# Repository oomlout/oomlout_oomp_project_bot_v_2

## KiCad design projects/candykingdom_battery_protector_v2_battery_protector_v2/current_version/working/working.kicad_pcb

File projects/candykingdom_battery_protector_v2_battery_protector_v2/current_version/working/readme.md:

# battery_protector_v2
 
## summary 
* id: candykingdom_battery_protector_v2_battery_protector_v2
* user: candykingdom
* name: battery_protector_v2
* board: battery_protector_v2
* repo: https://github.com/candykingdom/battery-protector-v2
* src_file_repo_kicad_pcb: battery-protector-v2.kicad_pcb
* src_file_repo_kicad_pcb_link: https://github.com/candykingdom/battery-protector-v2/tree/master/battery-protector-v2.kicad_pcb

* src_file_repo_sch: battery-protector-v2.sch
* src_file_repo_sch_link: https://github.com/candykingdom/battery-protector-v2/tree/master/battery-protector-v2.sch
* full details link: https://github.com/oomlout/oomlout_oomp_project_bot_v_2/tree/main/projects/candykingdom_battery_protector_v2_battery_protector_v2/current_version/working

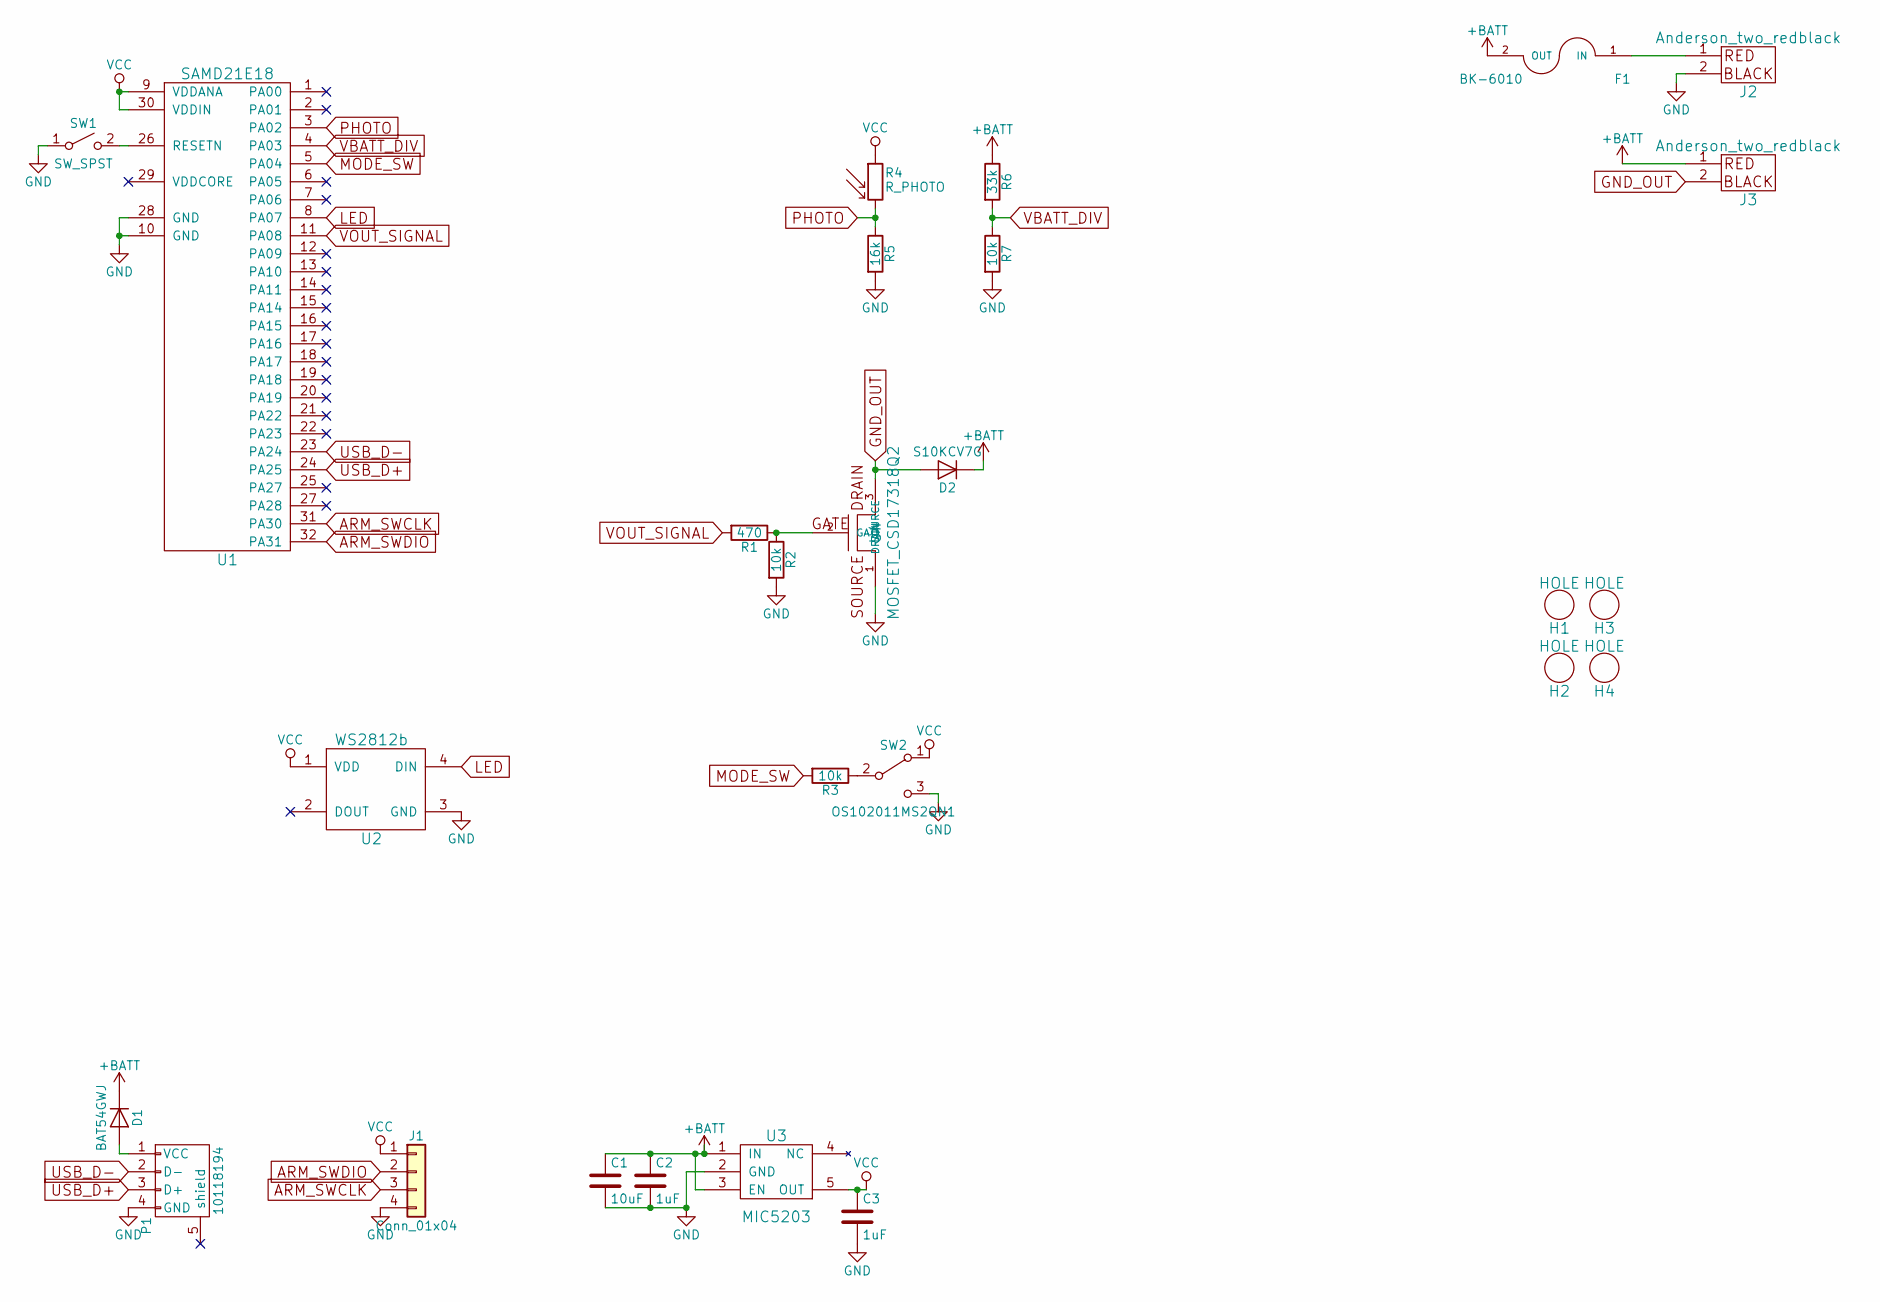
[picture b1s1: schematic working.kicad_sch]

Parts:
C1: 10uF; C_0805
C2, C3: 1uF; C_0603
D1: BAT54GWJ; D_SOD-123
D2: S10KCV7G; DIODE-DO-214AB
F1: BK-6010; FUSEHOLDER_ATC_Bk-6010
H1, H2, H3, H4: HOLE; HOLE_M4
J1: Conn_01x04; Pin_Header_Straight_1x04_Pitch2.54mm
J2, J3: Anderson_two_redblack; Anderson_1337G3_right_angle_bottom_two
P1: 10118194; FRAMATOME_10118194-0001LF
R1: 470; R_0603
R2, R3, R7: 10k; R_0603
R4: R_PHOTO
R5: 16k; R_0603
R6: 33k; R_0603
SW1: SW_SPST; TACTILE_SWITCH_SMD_4.6X2.8MM
SW2: OS102011MS2QN1; SW_2POS_OS102011MS2QN1
U1: SAMD21E18; TQFP32-08
U2: WS2812b; WS2812B
U3: MIC5203; SOT-23-5
U4: MOSFET_CSD17318Q2; TRANS_CSD17318Q2T

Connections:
+BATT: C1.1, C2.1, D1.1 (K), D2.1 (K), F1.2 (OUT), J3.1, R6.1, U3.1 (IN), U3.3 (EN)
ARM_SWCLK: J1.3, U1.31 (PA30)
ARM_SWDIO: J1.2, U1.32 (PA31)
GND: C1.2, C2.2, C3.2, J1.4, J2.2, P1.4 (GND), R2.2, R5.2, R7.2, SW1.1 (A), SW2.3 (C), U1.10 (GND), U1.28 (GND), U2.3 (GND), U3.2 (GND), U4.1 (SOURCE)
GND_OUT: D2.2 (A), J3.2, U4.3 (DRAIN)
LED: U1.8 (PA07), U2.4 (DIN)
MODE_SW: R3.2, U1.5 (PA04)
unnamed: D1.2 (A), P1.1 (VCC)
unnamed: F1.1 (IN), J2.1
unnamed: R1.1, R2.1, U4.2 (GATE)
unnamed: R3.1, SW2.2 (B)
unnamed: SW1.2 (B), U1.26 (RESETN)
PHOTO: R4.2, R5.1, U1.3 (PA02)
USB_D+: P1.3 (D+), U1.24 (PA25)
USB_D-: P1.2 (D-), U1.23 (PA24)
VBATT_DIV: R6.2, R7.1, U1.4 (PA03)
VCC: C3.1, J1.1, R4.1, SW2.1 (A), U1.9 (VDDANA), U1.30 (VDDIN), U2.1 (VDD), U3.5 (OUT)
VOUT_SIGNAL: R1.2, U1.11 (PA08)

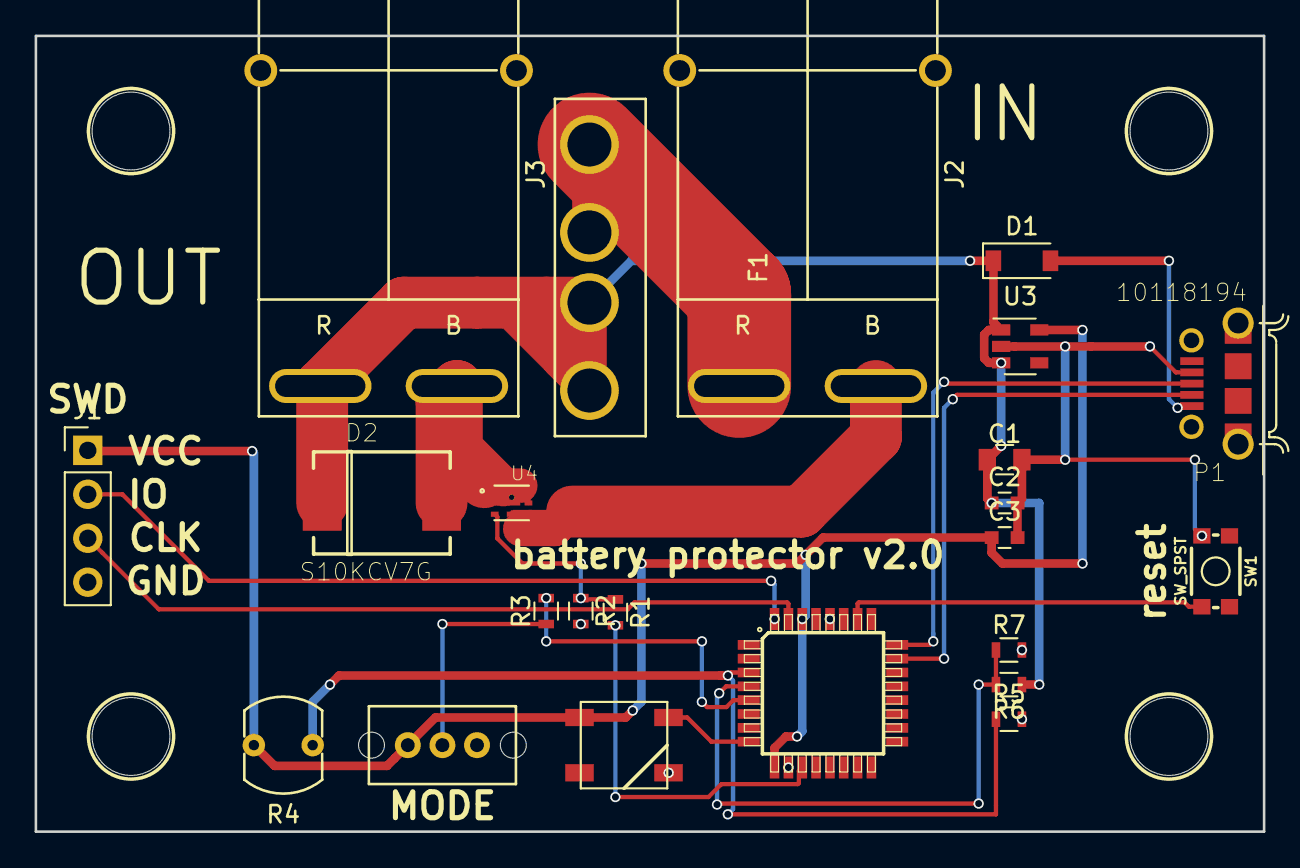
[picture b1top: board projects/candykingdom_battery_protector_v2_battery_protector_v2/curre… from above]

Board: 2 copper layers, 71.0 x 46.0 mm, 27 parts (0 on the bottom side), 18 nets.

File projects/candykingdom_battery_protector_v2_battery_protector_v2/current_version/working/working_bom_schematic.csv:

"Source:","C:\gh\oomlout_oomp_project_bot_v_2\projects\candykingdom_battery_protector_v2_battery_protector_v2\current_version\working\working.kicad_sch"
"Date:","27/09/2023 22:23:32"
"Tool:","Eeschema 7.0.6"
"Generator:","C:/Program Files/KiCad/7.0/bin/scripting/plugins/bom_csv_grouped_by_value_with_fp.py"
"Component Count:","27"
"Ref","Qnty","Value","Cmp name","Footprint","Description","Vendor","DNP"
"C1","1","10uF","C","Capacitors_SMD:C_0805","","",""
"C2, C3","2","1uF","C","Capacitors_SMD:C_0603","","",""
"D1","1","BAT54GWJ","D","Diodes_SMD:D_SOD-123","","",""
"D2","1","S10KCV7G","D","homebrew:DIODE-DO-214AB","","",""
"F1","1","BK-6010","POWER_FUSE","homebrew:FUSEHOLDER_ATC_Bk-6010","","",""
"H1, H2, H3, H4","4","HOLE","HOLE","homebrew:HOLE_M4","","",""
"J1","1","Conn_01x04","Conn_01x04","Pin_Headers:Pin_Header_Straight_1x04_Pitch2.54mm","","",""
"J2, J3","2","Anderson_two_redblack","Anderson_two_redblack","homebrew:Anderson_1337G3_right_angle_bottom_two","","",""
"P1","1","10118194","USB_B_POWER_SUPPLY","10118194-0001LF:FRAMATOME_10118194-0001LF","","",""
"R1","1","470","R","Resistors_SMD:R_0603","","",""
"R2, R3, R7","3","10k","R","Resistors_SMD:R_0603","","",""
"R4","1","R_PHOTO","R_PHOTO","homebrew:R_PHOTO","","",""
"R5","1","16k","R","Resistors_SMD:R_0603","","",""
"R6","1","33k","R","Resistors_SMD:R_0603","","",""
"SW1","1","SW_SPST","SW_SPST","Sparkfun-Switches:TACTILE_SWITCH_SMD_4.6X2.8MM","","",""
"SW2","1","OS102011MS2QN1","SW_SPDT","homebrew:SW_2POS_OS102011MS2QN1","","",""
"U1","1","SAMD21E18","SAMD21E18","homebrew:TQFP32-08","","",""
"U2","1","WS2812b","WS2812b","homebrew:WS2812B","","",""
"U3","1","MIC5203","MIC5225","TO_SOT_Packages_SMD:SOT-23-5","","",""
"U4","1","MOSFET_CSD17318Q2","MOSFET_CSD17318Q2","homebrew:TRANS_CSD17318Q2T","","",""

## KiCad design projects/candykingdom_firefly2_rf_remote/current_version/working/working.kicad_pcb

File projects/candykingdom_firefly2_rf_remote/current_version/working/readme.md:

# firefly2
 
## summary 
* id: candykingdom_firefly2_rf_remote
* user: candykingdom
* name: firefly2
* board: rf_remote
* repo: https://github.com/candykingdom/firefly2
* src_file_repo_kicad_pcb: hardware/remote/rf_remote.kicad_pcb
* src_file_repo_kicad_pcb_link: https://github.com/candykingdom/firefly2/tree/master/hardware/remote/rf_remote.kicad_pcb
* src_file_repo_kicad_sch: hardware/magnet-connector/magnet-connector.kicad_sch
* src_file_repo_kicad_sch_link: https://github.com/candykingdom/firefly2/tree/master/hardware/magnet-connector/magnet-connector.kicad_sch

* src_file_repo_sch: hardware/remote/rf_remote.sch
* src_file_repo_sch_link: https://github.com/candykingdom/firefly2/tree/master/hardware/remote/rf_remote.sch
* full details link: https://github.com/oomlout/oomlout_oomp_project_bot_v_2/tree/main/projects/candykingdom_firefly2_rf_remote/current_version/working

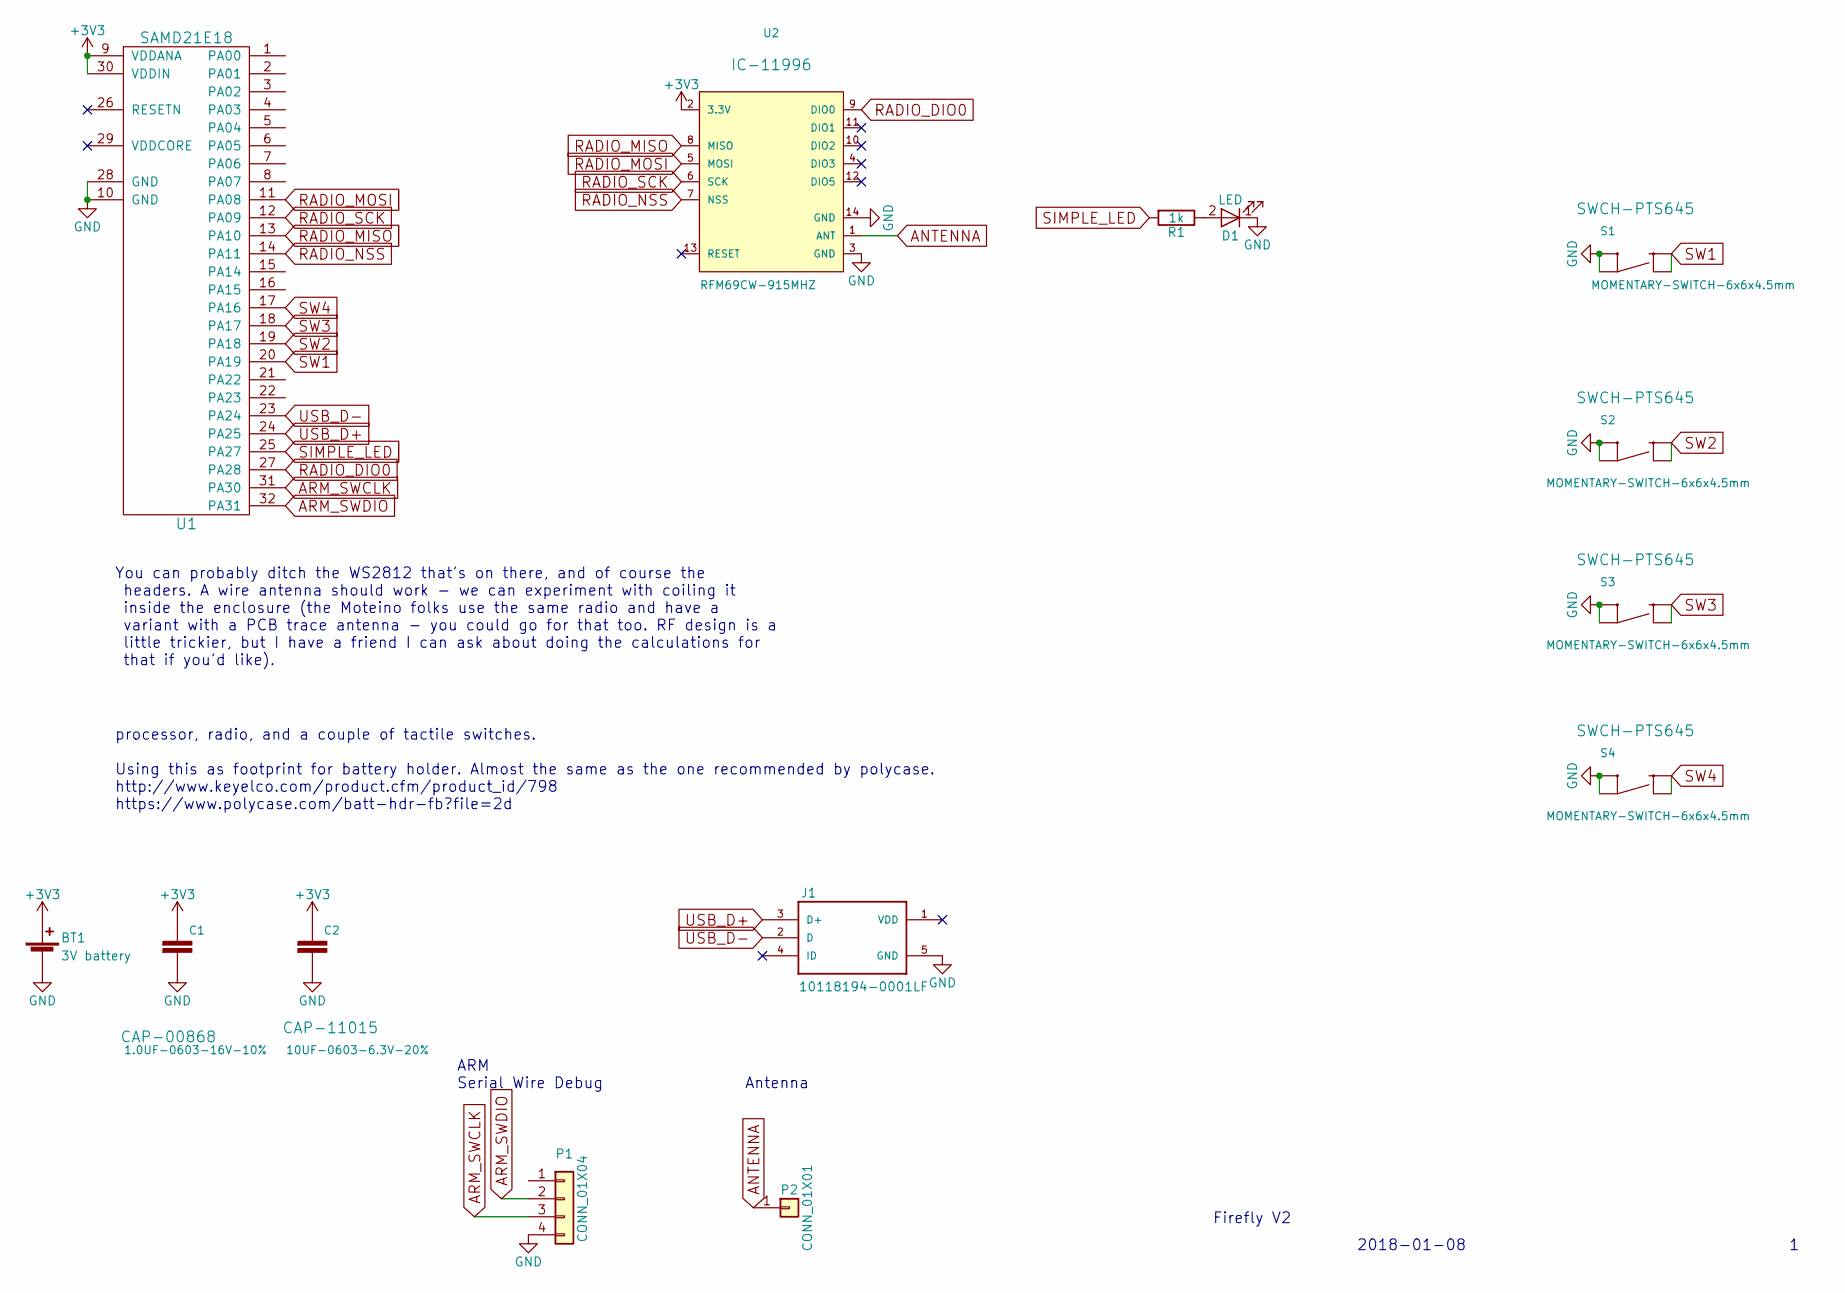
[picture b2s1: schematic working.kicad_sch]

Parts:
BT1: 3V battery; Keystone_3034_1x20mm-CoinCell
C1: 1.0UF-0603-16V-10%; C_0603
C2: 10UF-0603-6.3V-20%; C_0603
D1: LED; LED_0603
J1: 10118194-0001LF; FRAMATOME_10118194-0001LF
P1: CONN_01X04; 1X04
P2: CONN_01X01; 1X01
R1: 1k; R_0603_HandSoldering
S1, S2, S3, S4: MOMENTARY-SWITCH-6x6x4.5mm; 6x6x4.3mm button
U1: SAMD21E18; TQFP32-08
U2: RFM69CW-915MHZ; RFM69CW-XXXS2_

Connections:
+3V3: BT1.1 (+), C1.1, C2.1, U1.9 (VDDANA), U1.30 (VDDIN), U2.2 (3.3V)
ANTENNA: P2.1, U2.1 (ANT)
ARM_SWCLK: P1.3, U1.31 (PA30)
ARM_SWDIO: P1.2, U1.32 (PA31)
GND: BT1.2 (-), C1.2, C2.2, D1.1 (K), J1.5 (GND), P1.4, S1.1, S1.2, S2.1, S2.2, S3.1, S3.2, S4.1, S4.2, U1.10 (GND), U1.28 (GND), U2.3 (GND), U2.14 (GND)
unnamed: D1.2 (A), R1.1
RADIO_DIO0: U1.27 (PA28), U2.9 (DIO0)
RADIO_MISO: U1.13 (PA10), U2.8 (MISO)
RADIO_MOSI: U1.11 (PA08), U2.5 (MOSI)
RADIO_NSS: U1.14 (PA11), U2.7 (NSS)
RADIO_SCK: U1.12 (PA09), U2.6 (SCK)
SIMPLE_LED: R1.2, U1.25 (PA27)
SW1: S1.3, S1.4, U1.20 (PA19)
SW2: S2.3, S2.4, U1.19 (PA18)
SW3: S3.3, S3.4, U1.18 (PA17)
SW4: S4.3, S4.4, U1.17 (PA16)
USB_D+: J1.3 (D+), U1.24 (PA25)
USB_D-: J1.2 (D), U1.23 (PA24)

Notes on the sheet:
ARM Serial Wire Debug
You can probably ditch the WS2812 that's on there, and of course the headers. A wire antenna should work - we can experiment with coiling it inside the enclosure (the Moteino folks use the same radio and have a variant with a PCB trace antenna - you could go for that too. RF design is a little tric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
Firefly V2
Antenna
2018-01-08
processor, radio, and a couple of tactile switches. Using this as footprint for battery holder. Almost the same as the one recommended by polycase. http://www.keyelco.com/product.cfm/product_id/798 https://www.polycase.com/batt-hdr-fb?file=2d

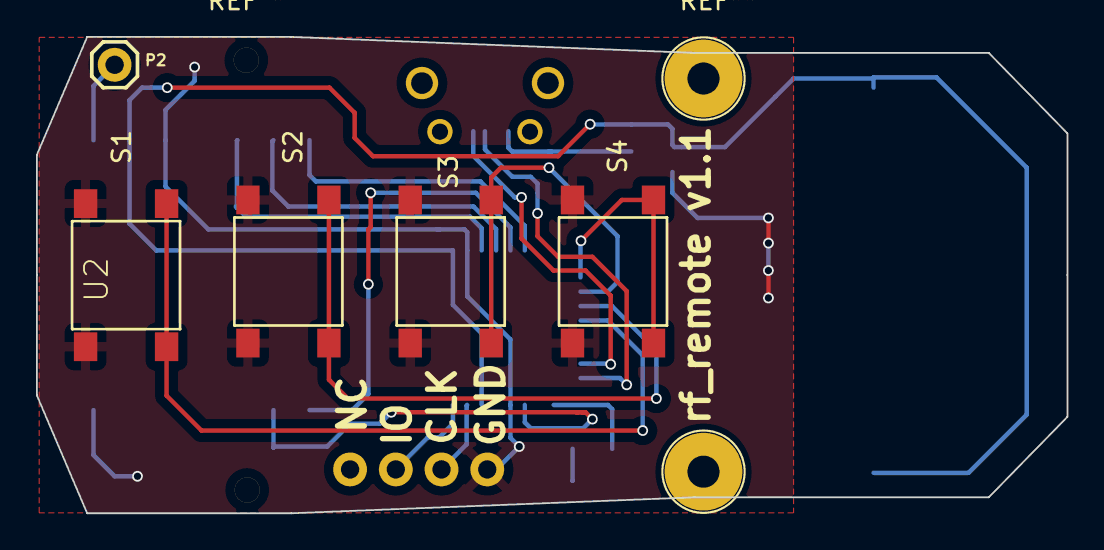
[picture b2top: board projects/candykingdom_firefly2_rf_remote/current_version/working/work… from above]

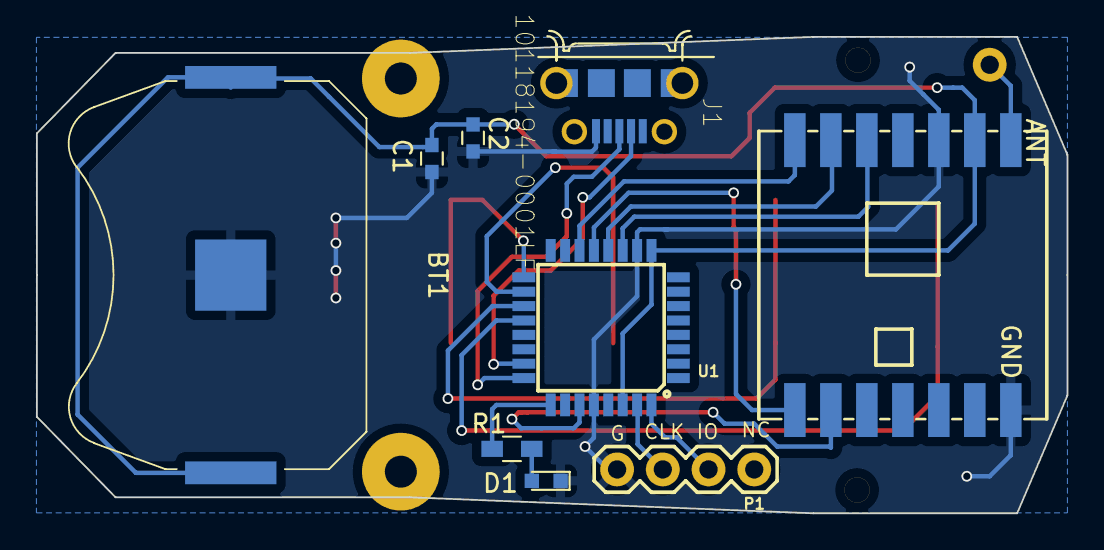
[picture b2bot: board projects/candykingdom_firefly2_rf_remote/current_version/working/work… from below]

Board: 2 copper layers, 57.3 x 26.5 mm, 14 parts (9 on the bottom side), 18 nets.

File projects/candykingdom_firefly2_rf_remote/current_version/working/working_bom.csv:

"Id";"Designator";"Footprint";"Quantity";"Designation";"Supplier and ref";
1;"REF**,REF**";"1pin";2;"1pin";;;
2;"REF**,REF**";"1pin";2;"1pin";;;
3;"S1,S2,S3,S4";"6x6x4.3mm button";4;"MOMENTARY-SWITCH-6x6x4.5mm";;;
4;"BT1";"Keystone_3034_1x20mm-CoinCell";1;"3V battery";;;
5;"D1";"LED_0603";1;"LED";;;
6;"R1";"R_0603_HandSoldering";1;"1k";;;
7;"U1";"TQFP32-08";1;"SAMD21E18";;;
8;"U2";"RFM69CW-XXXS2_";1;"RFM69CW-915MHZ";;;
9;"C1";"C_0603";1;"1.0UF-0603-16V-10%";;;
10;"C2";"C_0603";1;"10UF-0603-6.3V-20%";;;
11;"J1";"FRAMATOME_10118194-0001LF";1;"10118194-0001LF";;;

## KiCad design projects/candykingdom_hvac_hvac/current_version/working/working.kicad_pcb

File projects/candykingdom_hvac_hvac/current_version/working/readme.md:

# hvac
 
## summary 
* id: candykingdom_hvac_hvac
* user: candykingdom
* name: hvac
* board: hvac
* repo: https://github.com/candykingdom/hvac
* src_file_repo_kicad_pcb: hvac.kicad_pcb
* src_file_repo_kicad_pcb_link: https://github.com/candykingdom/hvac/tree/master/hvac.kicad_pcb

* src_file_repo_sch: hvac.sch
* src_file_repo_sch_link: https://github.com/candykingdom/hvac/tree/master/hvac.sch
* full details link: https://github.com/oomlout/oomlout_oomp_project_bot_v_2/tree/main/projects/candykingdom_hvac_hvac/current_version/working

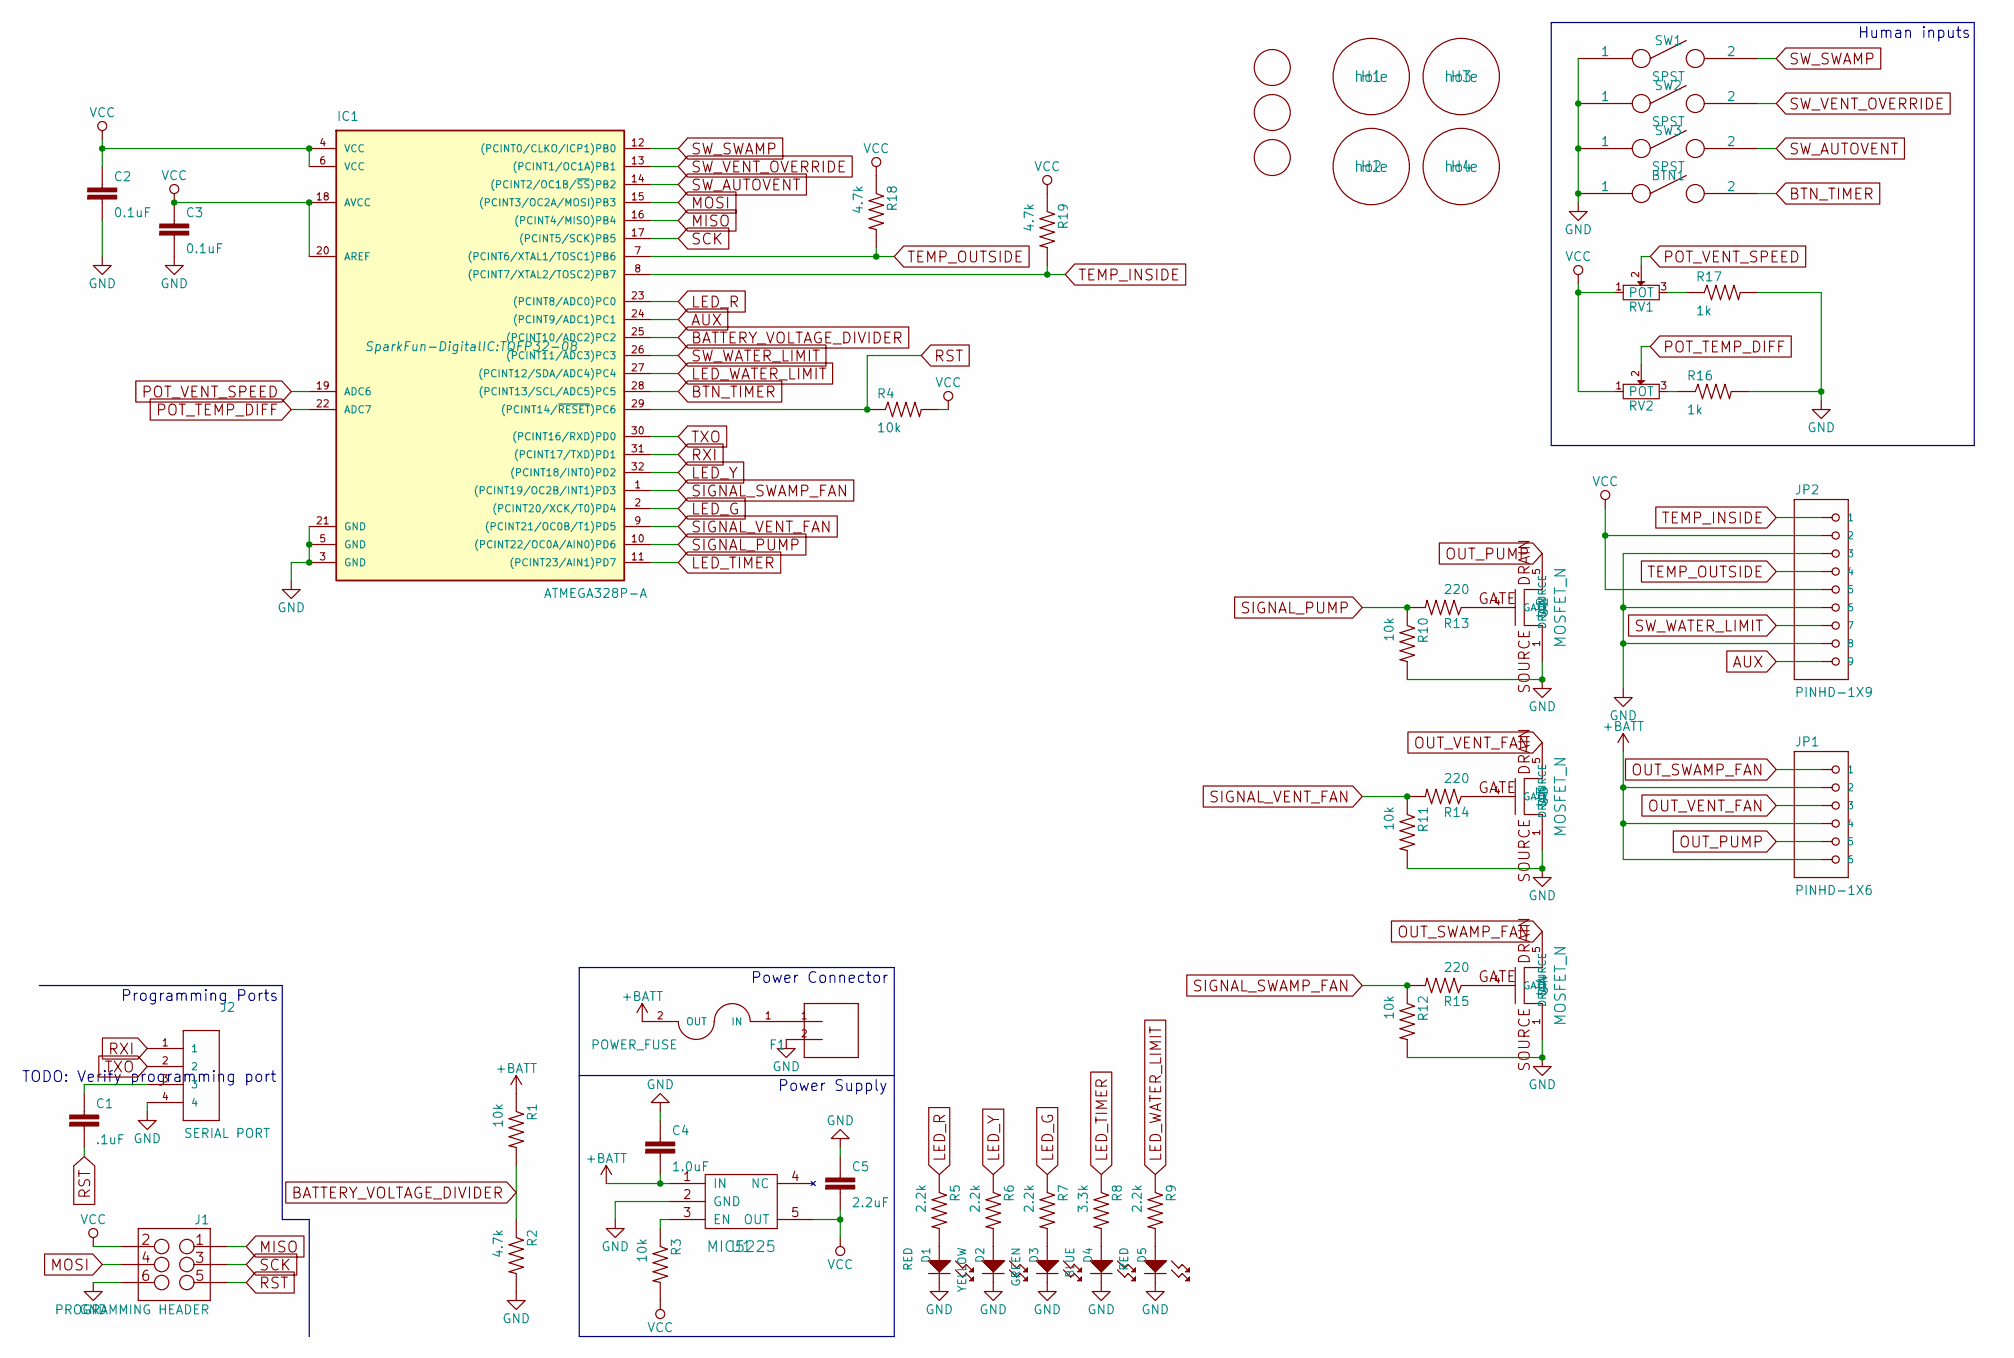
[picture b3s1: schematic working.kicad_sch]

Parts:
BTN1: SPST; PVA1-OA-H2
C1: .1uF; C_0603
C2, C3: 0.1uF; C_0603
C4: 1.0uF; C_0603
C5: 2.2uF; C_0603
D1, D5: RED; MF_LEDs-LED0603
D2: YELLOW; MF_LEDs-LED0603
D3: GREEN; MF_LEDs-LED0603
D4: BLUE; MF_LEDs-LED0603
F1: POWER_FUSE; FUSE-3550-2
H1, H2, H3, H4: hole; hole-m2.5
IC1: ATMEGA328P-A; TQFP32-08
J1: PROGRAMMING HEADER; 2X3
J2: SERIAL PORT; 1X04
J3: POWER_INPUT; 1x2-RIGHT_ANGLE-43160-1102
JP1: PINHD-1X6; 1x6-RIGHT_ANGLE-43160-3106
JP2: PINHD-1X9; 1x9-RIGHT_ANGLE-0534260910
M1, M2, M3: FIDUCIAL; FIDUCIAL_1MM
R1, R3, R4, R10, R11, R12: 10k; R_0402
R2, R18, R19: 4.7k; R_0402
R5, R6, R7, R9: 2.2k; R_0402
R8: 3.3k; R_0402
R13, R14, R15: 220; R_0402
R16, R17: 1k; R_0402
RV1, RV2: POT; PDB12-H4301-103BF
SW1, SW2, SW3: SPST; EG2355-ND
U1: MIC5225; SOT-23-5
U2, U3, U4: MOSFET_N; SOT-669_LFPAK_ThermalVias-1

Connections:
+BATT: C4.2, F1.2 (OUT), JP1.2, JP1.4, JP1.6, R1.1, U1.1 (IN)
AUX: IC1.24 ((PCINT9/ADC1)PC1), JP2.9
BATTERY_VOLTAGE_DIVIDER: IC1.25 ((PCINT10/ADC2)PC2), R1.2, R2.1
BTN_TIMER: BTN1.2, IC1.28 ((PCINT13/SCL/ADC5)PC5)
GND: BTN1.1, C2.2, C3.2, C4.1, C5.1, D1.CATH (CATHODE), D2.CATH (CATHODE), D3.CATH (CATHODE), D4.CATH (CATHODE), D5.CATH (CATHODE), IC1.3 (GND), IC1.5 (GND), IC1.21 (GND), J1.6, J2.4, J3.2, JP2.3, JP2.6, JP2.8, R2.2, R10.2, R11.2, R12.2, R16.2, R17.2, SW1.1, SW2.1, SW3.1, U1.2 (GND), U2.1 (SOURCE), U2.2 (SOURCE), U2.3 (SOURCE), U3.1 (SOURCE), U3.2 (SOURCE), U3.3 (SOURCE), U4.1 (SOURCE), U4.2 (SOURCE), U4.3 (SOURCE)
LED_G: IC1.2 ((PCINT20/XCK/T0)PD4), R7.1
LED_R: IC1.23 ((PCINT8/ADC0)PC0), R5.1
LED_TIMER: IC1.11 ((PCINT23/AIN1)PD7), R8.1
LED_WATER_LIMIT: IC1.27 ((PCINT12/SDA/ADC4)PC4), R9.1
LED_Y: IC1.32 ((PCINT18/INT0)PD2), R6.1
MISO: IC1.16 ((PCINT4/MISO)PB4), J1.1
MOSI: IC1.15 ((PCINT3/OC2A/MOSI)PB3), J1.4
unnamed: C1.1, J2.3
unnamed: D1.ANOD (ANODE), R5.2
unnamed: D2.ANOD (ANODE), R6.2
unnamed: D3.ANOD (ANODE), R7.2
unnamed: D4.ANOD (ANODE), R8.2
unnamed: D5.ANOD (ANODE), R9.2
unnamed: F1.1 (IN), J3.1
unnamed: R3.1, U1.3 (EN)
unnamed: R13.1, U2.4 (GATE)
unnamed: R14.1, U3.4 (GATE)
unnamed: R15.1, U4.4 (GATE)
unnamed: R16.1, RV2.3
unnamed: R17.1, RV1.3
OUT_PUMP: JP1.5, U2.5 (DRAIN)
OUT_SWAMP_FAN: JP1.1, U4.5 (DRAIN)
OUT_VENT_FAN: JP1.3, U3.5 (DRAIN)
POT_TEMP_DIFF: IC1.22 (ADC7), RV2.2
POT_VENT_SPEED: IC1.19 (ADC6), RV1.2
RST: C1.2, IC1.29 ((PCINT14/~RESET)PC6), J1.5, R4.1
RXI: IC1.31 ((PCINT17/TXD)PD1), J2.1
SCK: IC1.17 ((PCINT5/SCK)PB5), J1.3
SIGNAL_PUMP: IC1.10 ((PCINT22/OC0A/AIN0)PD6), R10.1, R13.2
SIGNAL_SWAMP_FAN: IC1.1 ((PCINT19/OC2B/INT1)PD3), R12.1, R15.2
SIGNAL_VENT_FAN: IC1.9 ((PCINT21/OC0B/T1)PD5), R11.1, R14.2
SW_AUTOVENT: IC1.14 ((PCINT2/OC1B/~SS)PB2), SW3.2
SW_SWAMP: IC1.12 ((PCINT0/CLKO/ICP1)PB0), SW1.2
SW_VENT_OVERRIDE: IC1.13 ((PCINT1/OC1A)PB1), SW2.2
SW_WATER_LIMIT: IC1.26 ((PCINT11/ADC3)PC3), JP2.7
TEMP_INSIDE: IC1.8 ((PCINT7/XTAL2/TOSC2)PB7), JP2.1, R19.2
TEMP_OUTSIDE: IC1.7 ((PCINT6/XTAL1/TOSC1)PB6), JP2.4, R18.2
TXO: IC1.30 ((PCINT16/RXD)PD0), J2.2
VCC: C2.1, C3.1, C5.2, IC1.4 (VCC), IC1.6 (VCC), IC1.18 (AVCC), IC1.20 (AREF), J1.2, JP2.2, JP2.5, R3.2, R4.2, R18.1, R19.1, RV1.1, RV2.1, U1.5 (OUT)

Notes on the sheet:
Human inputs
Power Supply
Power Connector
Programming Ports
TODO: Verify programming port

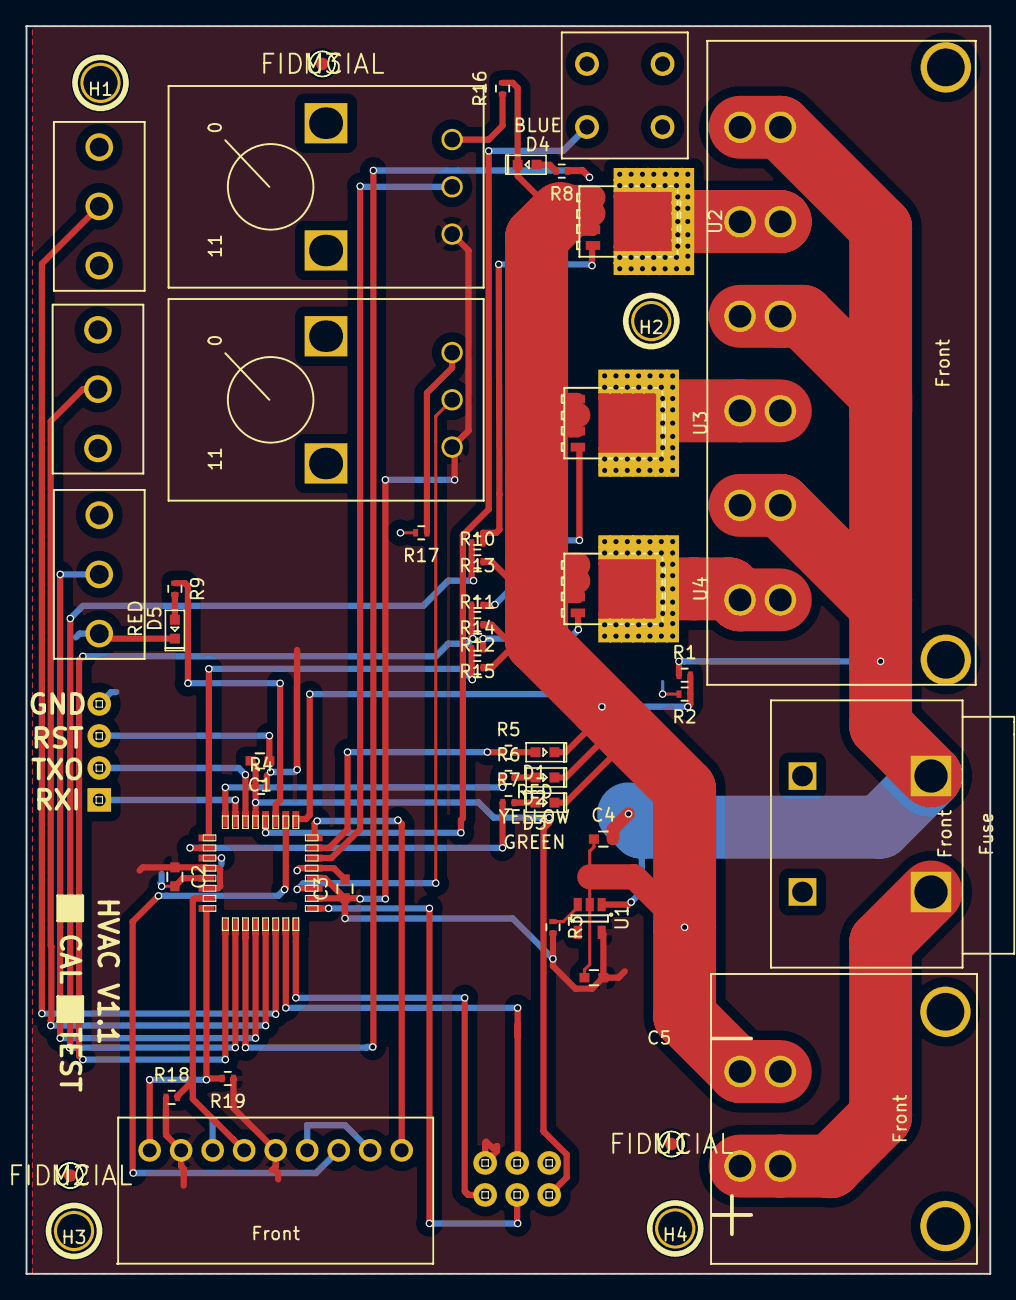
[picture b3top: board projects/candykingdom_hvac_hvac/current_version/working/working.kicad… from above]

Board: 2 copper layers, 76.5 x 99.0 mm, 53 parts (0 on the bottom side), 44 nets.

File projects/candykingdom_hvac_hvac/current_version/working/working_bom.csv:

"Id";"Designator";"Footprint";"Quantity";"Designation";"Supplier and ref";
1;"BTN1";"PVA1-OA-H2";1;"SPST";;;
2;"C1";"C_0603";1;".1uF";;;
3;"C2,C3";"C_0603";2;"0.1uF";;;
4;"C4";"C_0603";1;"1.0uF";;;
5;"C5";"C_0603";1;"2.2uF";;;
6;"D1,D5";"MF_LEDs-LED0603";2;"RED";;;
7;"D2";"MF_LEDs-LED0603";1;"YELLOW";;;
8;"D3";"MF_LEDs-LED0603";1;"GREEN";;;
9;"D4";"MF_LEDs-LED0603";1;"BLUE";;;
10;"F1";"FUSE-3550-2";1;"POWER_FUSE";;;
11;"IC1";"TQFP32-08";1;"ATMEGA328P-A";;;
12;"J3";"1x2-RIGHT_ANGLE-43160-1102";1;"POWER_INPUT";;;
13;"JP1";"1x6-RIGHT_ANGLE-43160-3106";1;"PINHD-1X6";;;
14;"JP2";"1x9-RIGHT_ANGLE-0534260910";1;"PINHD-1X9";;;
15;"R1,R3,R4,R10,R11,R12";"R_0402";6;"10k";;;
16;"R2,R18,R19";"R_0402";3;"4.7k";;;
17;"R5,R6,R7,R9";"R_0402";4;"2.2k";;;
18;"R8";"R_0402";1;"3.3k";;;
19;"R13,R14,R15";"R_0402";3;"220";;;
20;"R16,R17";"R_0402";2;"1k";;;
21;"RV1,RV2";"PDB12-H4301-103BF";2;"POT";;;
22;"SW1,SW2,SW3";"EG2355-ND";3;"SPST";;;
23;"U1";"SOT-23-5";1;"MIC5225";;;
24;"U2,U3,U4";"SOT-669_LFPAK_ThermalVias-1";3;"MOSFET_N";;;
25;"H1,H2,H3,H4";"hole-m2.5";4;"hole";;;
26;"M1,M2,M3";"FIDUCIAL_1MM";3;"FIDUCIAL";;;
